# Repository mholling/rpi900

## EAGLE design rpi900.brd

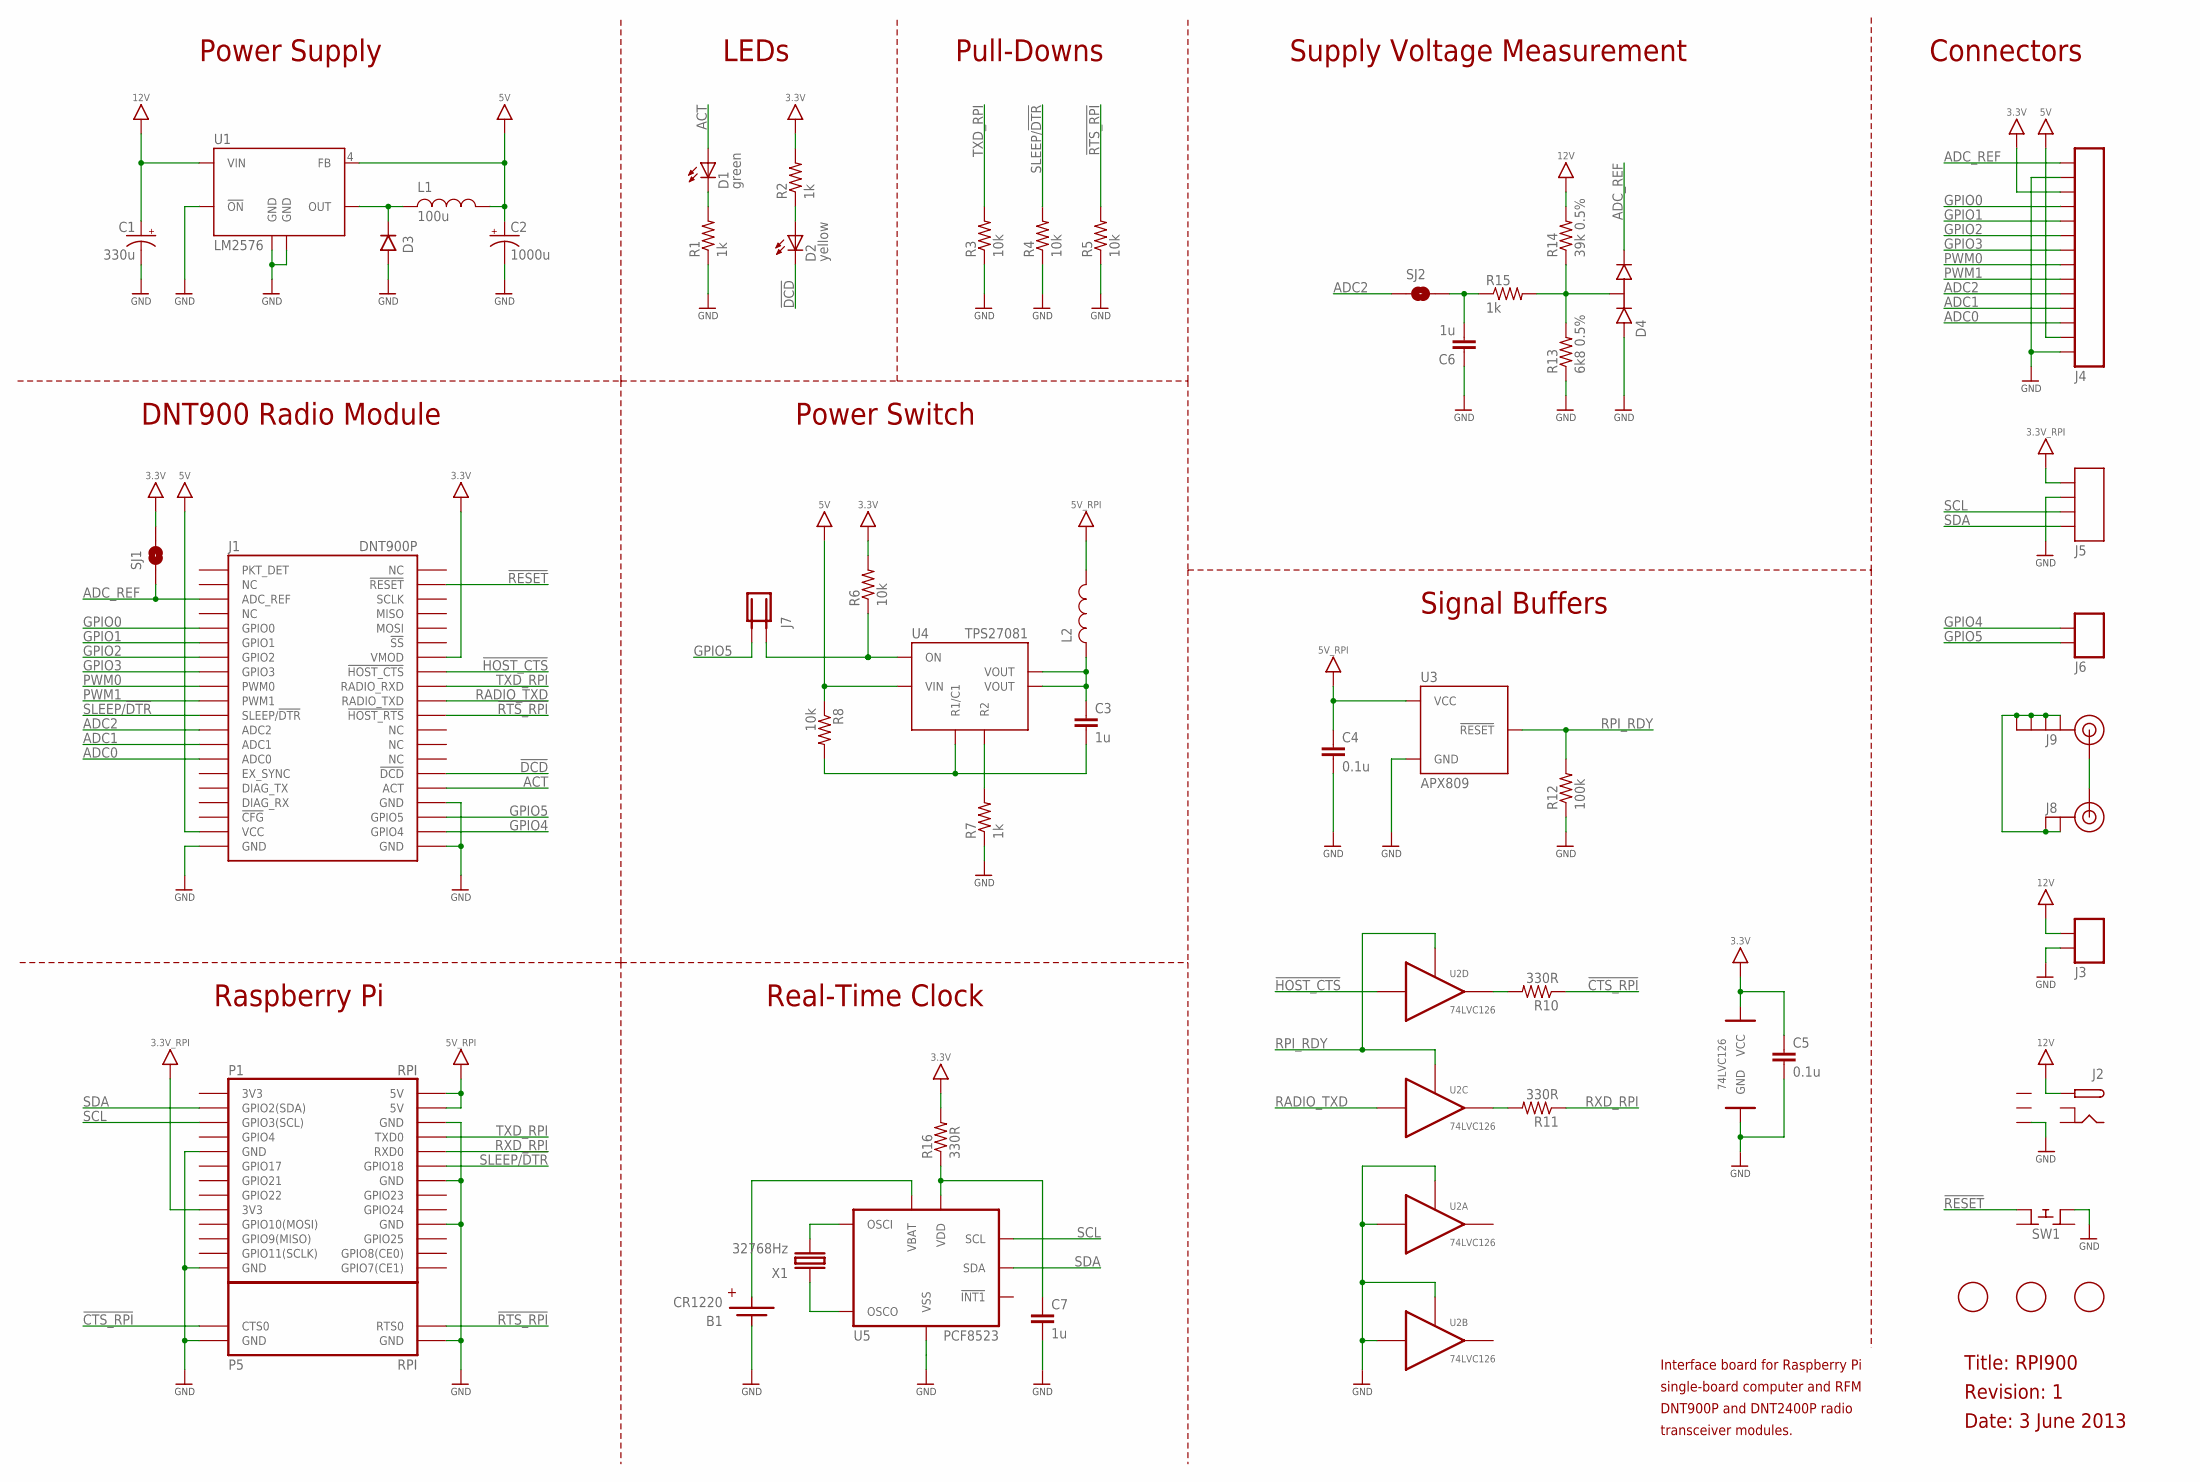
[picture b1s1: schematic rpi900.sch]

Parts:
B1: CR1220; 3000
C1: 330u; 140CLH-1010
C2: 1000u; 140CLH-1010
C3, C6, C7: 1u; 0805
C4, C5: 0.1u; 0805
D1: green; 0805-LED
D2: yellow; 0805-LED
D3: MURS320T3G; DO-214AB
D4: BAT54S; SOT23
F1, F2, F3: FIDUCIAL; FIDUCIAL_1MM
J1: DNT900P
J2: DCBARRELPTH; PJ-002A
J3: TERMINAL-2P-3.5MM
J4: TERMINAL-14P; TERMINAL-14P-0.1
J5: TERMINAL-4P; TERMINAL-4P-0.1
J6: TERMINAL-2P-0.1
J7: JUMPER
J8: U.FL
J9: SMAPTH; SMA-PTH
L1: 100u; SRR1280
L2: FERRITE-BEAD; 0805
P: RPI
R1, R2, R7, R15: 1k; 0805
R3, R4, R5, R6, R8: 10k; 0805
R10, R11, R16: 330R; 0805
R12: 100k; 0805
R13: 6k8 0.5%; 0805
R14: 39k 0.5%; 0805
SJ1: SOLDERJUMPERTRACE; SJ_2S-TRACE
SJ2: SOLDERJUMPERNO; SJ_2S-NO
SW1: FSM4JH; JSM4JH
U1: LM2576; TO-263
U2: 74LVC126; SO14
U3: APX809; SOT23
U4: TPS27081; TSOT-23-6
U5: PCF8523; SO08
X1: 32768Hz; CFS-206

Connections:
3.3V: C5.1, J1.P$34 (VMOD), J4.3, R2.2, R6.2, R16.2, SJ1.2, U2.14 (VCC)
3.3V_RPI: J5.1, P.P$17 (3V3)
3V3: P.P$1 (3V3)
5V: C2.+, J1.P$19 (VCC), J4.13, L1.P$2, R8.1, U1.4 (FB), U4.P$4 (VIN)
5V_RPI: C4.1, L2.2, P.P$2 (5V), P.P$4 (5V), U3.P$3 (VCC)
12V: C1.+, J2.CENTRE, J3.P$1, R14.2, U1.1 (VIN)
!CTS_RPI: P.P$31 (CTS0), R10.1
!DCD: D2.K (C), J1.P$26 (!DCD)
!HOST_CTS: J1.P$33 (!HOST_CTS), U2.12 (X)
!RESET: J1.P$39 (!RESET), SW1.P$3 (3)
!RTS_RPI: J1.P$30 (!HOST_RTS), P.P$32 (RTS0), R5.2
ACT: D1.A, J1.P$25 (ACT)
ADC0: J1.P$14 (ADC0), J4.12
ADC1: J1.P$13 (ADC1), J4.11
ADC2: J1.P$12 (ADC2), J4.10, SJ2.1
ADC_REF: D4.P$2, J1.P$3 (ADC_REF), J4.1, SJ1.1
CENTRE-BOTTOM: J2.CENTRE-BOTTOM
EN_RPI: J7.1, R6.1, U4.P$5 (ON)
GND: B1.NEGATIVE, C1.-, C2.-, C4.2, C5.2, C6.1, C7.2, D3.A, D4.P$1, J1.P$20 (GND), J1.P$21 (GND), J1.P$24 (GND), J2.SLEEVE-BOTTOM, J3.P$2, J4.2, J4.14, J5.2, P.P$6 (GND), P.P$9 (GND), P.P$14 (GND), P.P$20 (GND), P.P$25 (GND), P.P$33 (GND), P.P$34 (GND), R1.1, R3.1, R4.1, R5.1, R7.1, R12.1, R13.1, SW1.P$1 (1), U1.3 (GND), U1.5 (!ON), U1.TAB (GND), U2.1 (!OE), U2.2 (X), U2.4 (!OE), U2.5 (X), U2.7 (GND), U3.P$1 (GND), U5.4 (VSS)
GPIO0: J1.P$5 (GPIO0), J4.4
GPIO1: J1.P$6 (GPIO1), J4.5
GPIO2: J1.P$7 (GPIO2), J4.6
GPIO3: J1.P$8 (GPIO3), J4.7
GPIO4: J1.P$22 (GPIO4), J6.1
GPIO5: J1.P$23 (GPIO5), J6.2, J7.2
unnamed: D1.K (C), R1.2
unnamed: D2.A, R2.1
unnamed: D4.P$3, R13.2, R14.1, R15.2
unnamed: R10.2, U2.11 (Y)
unnamed: J8.P$3 (SIGNAL), J9.SIG (SIGNAL)
unnamed: R11.2, U2.8 (Y)
unnamed: C6.2, R15.1, SJ2.2
unnamed: R7.2, U4.P$1 (R2)
unnamed: U5.1 (OSCI), X1.P$2
unnamed: J8.P$1 (GND), J8.P$2 (GND), J9.GND@0 (GND), J9.GND@1 (GND), J9.GND@2 (GND), J9.GND@3 (GND)
unnamed: C7.1, R16.1, U5.8 (VDD)
unnamed: U5.2 (OSCO), X1.P$1
OUT: D3.K, L1.P$1, U1.2 (OUT)
PWM0: J1.P$9 (PWM0), J4.8
PWM1: J1.P$10 (PWM1), J4.9
R1/C1: C3.2, R8.2, U4.P$6 (R1/C1)
RADIO_TXD: J1.P$31 (RADIO_TXD), U2.9 (X)
RPI_RDY: R12.2, U2.10 (!OE), U2.13 (!OE), U3.P$2 (!RESET)
RXD_RPI: P.P$10 (RXD0), R11.1
SCL: J5.3, P.P$5 (GPIO3(SCL)), U5.6 (SCL)
SDA: J5.4, P.P$3 (GPIO2(SDA)), U5.5 (SDA)
SHUNT: J2.SHUNT
SHUNT-BOTTOM: J2.SHUNT-BOTTOM
SLEEP/!DTR: J1.P$11 (SLEEP/!DTR), P.P$12 (GPIO18), R4.2
SLEEVE: J2.SLEEVE
TXD_RPI: J1.P$32 (RADIO_RXD), P.P$8 (TXD0), R3.2
VBAT: B1.POSITIVE1 (POSITIVE), U5.3 (VBAT)
VOUT: C3.1, L2.1, U4.P$2 (VOUT), U4.P$3 (VOUT)

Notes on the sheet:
Power Supply
DNT900 Radio Module
Raspberry Pi
Real-Time Clock
Power Switch
LEDs
Connectors
Signal Buffers
Supply Voltage Measurement
Pull-Downs
Revision: 1
Title: RPI900
Interface board for Raspberry Pi
Date: 3 June 2013
single-board computer and RFM
DNT900P and DNT2400P radio
transceiver modules.

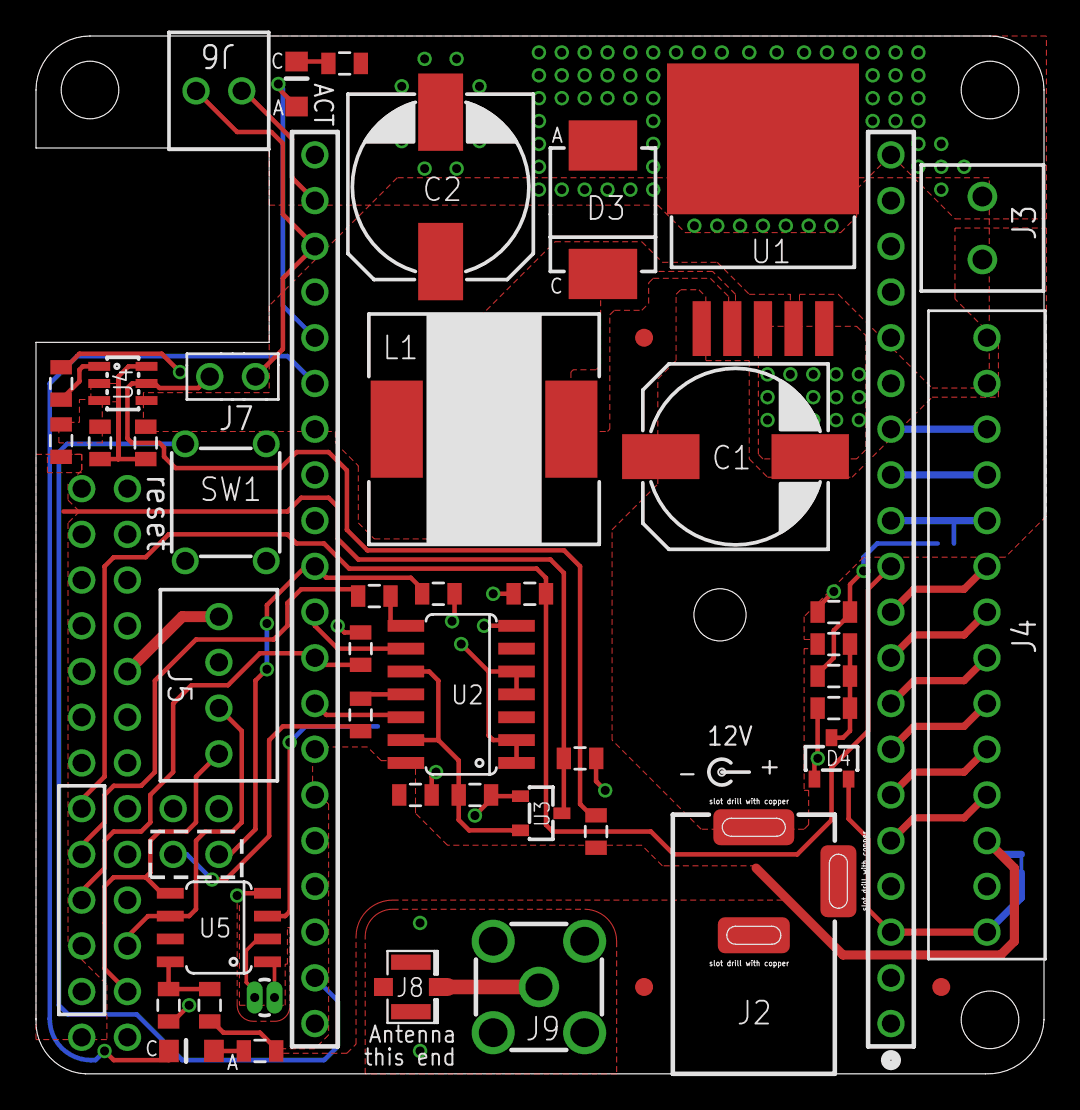
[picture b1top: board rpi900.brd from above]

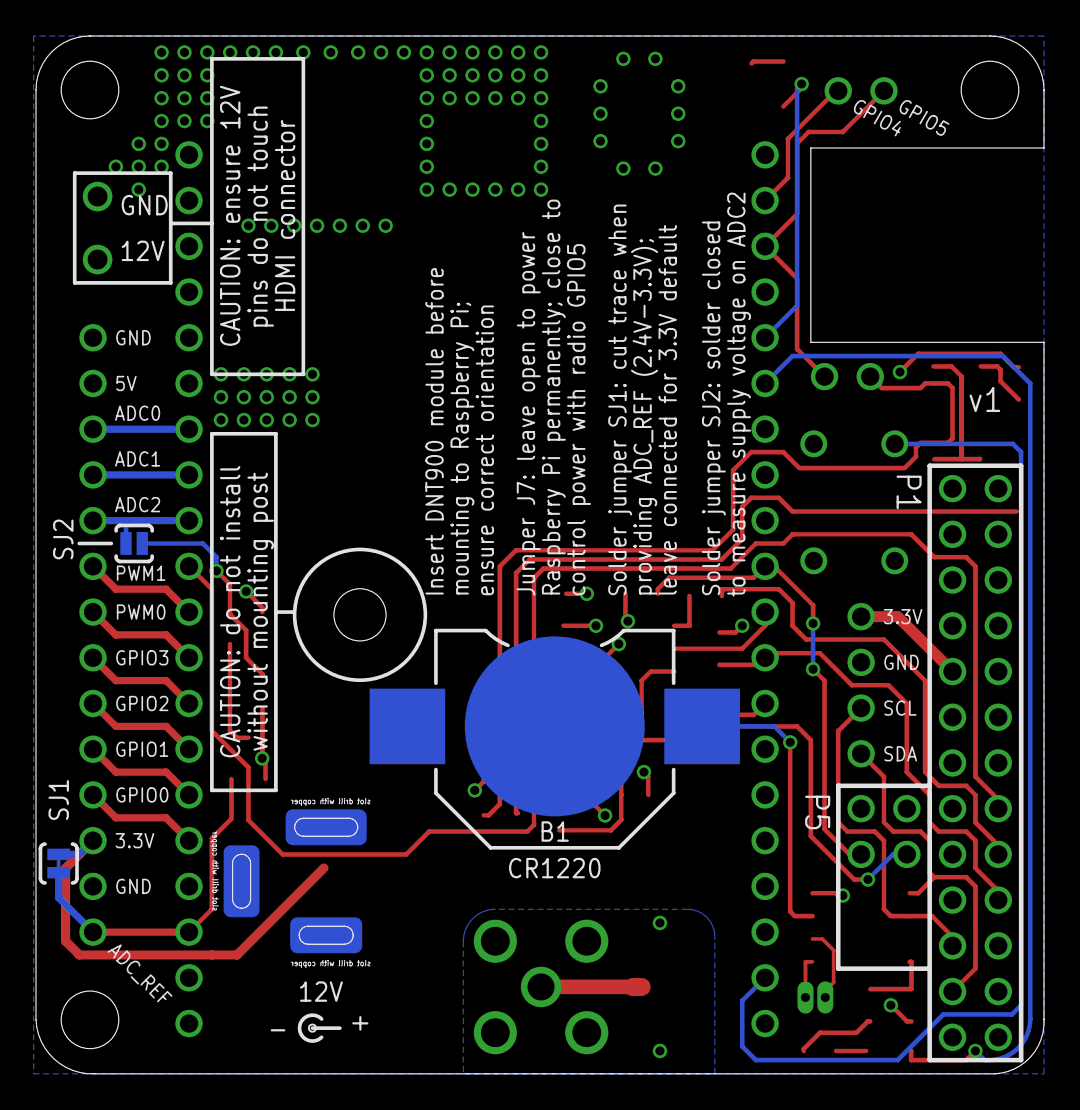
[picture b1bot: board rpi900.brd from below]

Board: 2 copper layers, 56.0 x 57.7 mm, 54 parts (3 on the bottom side), 48 nets.

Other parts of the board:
U$9, U$28, U$46: CORNER-SHARP

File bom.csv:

Qty,Part Reference,Part Number,Manufacturer,DigiKey Part Number,Description,Footprint
1,U1,LM2576D2T-005G,ON Semiconductor,LM2576D2T-005GOS-ND,switching regulator,TO-263-6
1,U2,SN74LVC126ADR,Texas Instruments,296-8457-1-ND,quad buffer,14-SOIC
1,U3,APX809-44SAG-7,Diodes Inc,APX809-44SAGDICT-ND,microprocessor reset,SOT-23-3
1,U4,TPS27081ADDCR,Texas Instruments,296-34970-1-ND,high-side load switch,TSOT-23-6
1,U5,"PCF8523T/1,118",NXP Semiconductors,568-5306-1-ND,real-time clock,8-SOIC
1,D1,LTST-C171KGKT,Lite-On Inc,160-1426-1-ND,LED green,0805
1,D2,LTST-C171KSKT,Lite-On Inc,160-1428-1-ND,LED yellow,0805
1,D3,MBRS340T3G,ON Semiconductor,MBRS340T3GOSCT-ND,schottky diode,DO-214AB
1,D4,BAT54SLT1G,ON Semiconductor,BAT54SLT1GOSCT-ND,dual schottky diode,SOT-23-3
4,R1 R2 R7 R15,RMCF0805JT1K00,Stackpole Electronics Inc,RMCF0805JT1K00CT-ND,resistor 1k,0805
5,R3 R4 R5 R6 R8,RMCF0805JT10K0,Stackpole Electronics Inc,RMCF0805JT10K0CT-ND,resistor 10k,0805
1,R12,RMCF0805JT100K,Stackpole Electronics Inc,RMCF0805JT100KCT-ND,resistor 100k,0805
3,R10 R11 R16,RMCF0805JT330R,Stackpole Electronics Inc,RMCF0805JT330RCT-ND,resistor 330R,0805
1,R13,RR1220P-682-D,Susumu,RR12P6.8KDCT-ND,resistor 6k8 0.5%,0805
1,R14,RR1220P-393-D,Susumu,RR12P39.0KDCT-ND,resistor 39k 0.5%,0805
1,C1,EEE-FK1V331P,Panasonic Electronic Components,PCE3841CT-ND,aluminum capacitor 330uF,SMD 10.3mm x 10.3mm
1,C2,EEE-FK1A102P,Panasonic Electronic Components,PCE3772CT-ND,aluminum capacitor 1000uF,SMD 10.3mm x 10.3mm
3,C3 C6 C7,CC0805KKX7R7BB105,Yageo,311-1365-1-ND,ceramic capacitor 1.0uF,0805
2,C4 C5,C0805C104K5RACTU,Kemet,399-1170-1-ND,ceramic capacitor 0.1uF,0805
1,L1,SRR1280-101M,Bourns Inc,SRR1280-101MTR-ND,inductor 100uH,SMD 12.5mm x 12.5mm
1,L2,MH2029-600Y,Bourns Inc,MH2029-600YCT-ND,ferrite bead,0805
1,X1,CFS206-32.768KDZF-UB,Citizen,300-8303-ND,crystal 32.768kHz,through-hole 2mm x 6mm
2,J1A J1B,PPPC201LFBN-RC,Sullins Connector Solutions,S7053-ND,header female 1x20,"through-hole 0.1"" 1x20"
1,J2,PJ-002A,CUI Inc,CP-002A-ND,DC power jack 2.1mm/5.5m,through-hole
1,J3,OSTTE020104,On Shore Technology Inc,ED2740-ND,terminal block 2p,through-hole 3.5mm 2p
1,J7,M20-9990245,Harwin Inc,952-2261-ND,jumper/header,"through-hole 0.1"" 1x2"
1,J8,734120110,Molex Inc,WM5587CT-ND,ultraminiature coax connector,SMD 4mm x 4mm
1,J9,5-1814400-1,TE Connectivity,A97593-ND,SMA connector right angle,through-hole
1,P1,PPPC132LFBN-RC,Sullins Connector Solutions,S7116-ND,header female 2x13,"through-hole 0.1"" 2x13"
1,P5,PPPC042LFBN-RC,Sullins Connector Solutions,S7107-ND,header female 2x4,"through-hole 0.1"" 2x4"
1,B1,3000,Keystone Electronics,3000K-ND,12mm coin battery holder,SMD
1,SW1,FSM4JH,TE Connectivity,450-1650-ND,tactile switch,through-hole 6mm x 6mm
7,J4 J5 J6,,,,optional connectors,"through-hole 0.1"""

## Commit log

2013-06-03 adding files for revision 1 hardware
2013-07-08 added kernel patch for high-speed serial
2013-07-08 license
2013-11-13 added patch for Arch Linux kernel package to enable rtc
2013-11-13 renamed patch
2013-12-01 new PKGBUILD patch for linux-raspberrypi-3.10.21
2013-12-24 make config patch more robust
2014-04-08 add PKGBUILD patch to increase UART0_CLOCK for high-speed serial
